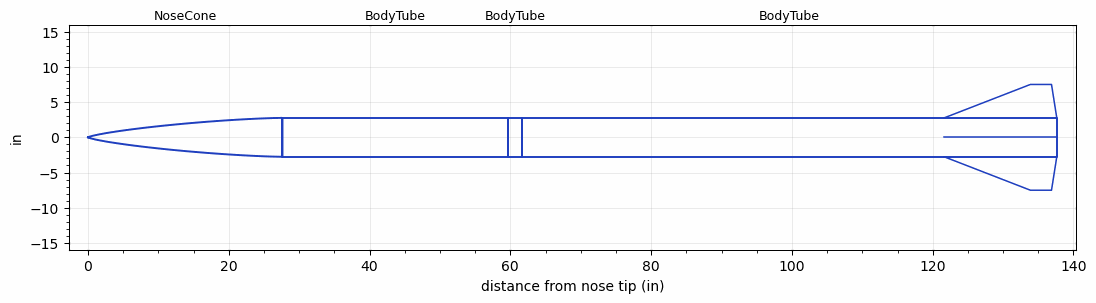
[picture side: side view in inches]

<RASAeroDocument>
 <FileVersion>2</FileVersion>
 <RocketDesign>
  <NoseCone>
   <Length>27.6249</Length>
   <Diameter>5.525</Diameter>
   <Shape>Von Karman Ogive</Shape>
   <Location>0</Location>
  </NoseCone>
  <BodyTube>
   <Length>31.9999</Length>
   <Diameter>5.525</Diameter>
   <Location>27.6249</Location>
  </BodyTube>
  <BodyTube>
   <Length>2</Length>
   <Diameter>5.525</Diameter>
   <Location>59.6249</Location>
  </BodyTube>
  <BodyTube>
   <Length>75.9998</Length>
   <Diameter>5.525</Diameter>
   <Location>61.6249</Location>
   <Fin>
    <Count>4</Count>
    <Chord>16</Chord>
    <Span>4.75</Span>
    <SweepDistance>12.2515</SweepDistance>
    <TipChord>3</TipChord>
    <Thickness>0.5</Thickness>
    <Location>16</Location>
    <AirfoilSection>Subsonic NACA</AirfoilSection>
   </Fin>
  </BodyTube>
  <Surface>Smooth Paint</Surface>
  <ModifiedBarrowman>False</ModifiedBarrowman>
  <Turbulence>False</Turbulence>
  <UseBooster1>False</UseBooster1>
  <UseBooster2>False</UseBooster2>
 </RocketDesign>
 <LaunchSite>
  <Altitude>3005</Altitude>
  <Pressure>29.92</Pressure>
  <RodAngle>0</RodAngle>
  <RodLength>17</RodLength>
  <Temperature>100</Temperature>
  <WindSpeed>5</WindSpeed>
 </LaunchSite>
 <Recovery>
  <Altitude1>656.168</Altitude1>
  <Altitude2>1500</Altitude2>
  <DeviceType1>Parachute</DeviceType1>
  <DeviceType2>Parachute</DeviceType2>
  <Event1>True</Event1>
  <Event2>True</Event2>
  <Size1>36</Size1>
  <Size2>143.9997</Size2>
  <EventType1>Apogee</EventType1>
  <EventType2>Altitude</EventType2>
  <CD1>0.97</CD1>
  <CD2>2.2</CD2>
 </Recovery>
 <SimulationList>
  <Simulation>
   <SustainerEngine>O5500X  (AT)</SustainerEngine>
   <SustainerLaunchWt>71.7</SustainerLaunchWt>
   <SustainerNozzleDiameter>3</SustainerNozzleDiameter>
   <SustainerCG>94.13</SustainerCG>
   <SustainerIgnitionDelay>0</SustainerIgnitionDelay>
   <Booster1SeparationDelay>0</Booster1SeparationDelay>
   <Booster1IgnitionDelay>0</Booster1IgnitionDelay>
   <IncludeBooster1>False</IncludeBooster1>
   <Booster2Delay>0</Booster2Delay>
   <IncludeBooster2>False</IncludeBooster2>
   <TimetoApogee>40.88914</TimetoApogee>
   <MaxAltitude>32501.06</MaxAltitude>
   <MaxVelocity>2160.328</MaxVelocity>
  </Simulation>
  <Simulation>
   <SustainerLaunchWt>71.7356</SustainerLaunchWt>
   <SustainerCG>94.1344</SustainerCG>
   <SustainerIgnitionDelay>0</SustainerIgnitionDelay>
   <Booster1SeparationDelay>0</Booster1SeparationDelay>
   <Booster1IgnitionDelay>0</Booster1IgnitionDelay>
   <IncludeBooster1>False</IncludeBooster1>
   <Booster2Delay>0</Booster2Delay>
   <IncludeBooster2>False</IncludeBooster2>
  </Simulation>
  <Simulation>
   <SustainerLaunchWt>70.6278</SustainerLaunchWt>
   <SustainerCG>96.5985</SustainerCG>
   <SustainerIgnitionDelay>0</SustainerIgnitionDelay>
   <Booster1SeparationDelay>0</Booster1SeparationDelay>
   <Booster1IgnitionDelay>0</Booster1IgnitionDelay>
   <IncludeBooster1>False</IncludeBooster1>
   <Booster2Delay>0</Booster2Delay>
   <IncludeBooster2>False</IncludeBooster2>
  </Simulation>
  <Simulation>
   <SustainerLaunchWt>64.0745</SustainerLaunchWt>
   <SustainerCG>96.9611</SustainerCG>
   <SustainerIgnitionDelay>0</SustainerIgnitionDelay>
   <Booster1SeparationDelay>0</Booster1SeparationDelay>
   <Booster1IgnitionDelay>0</Booster1IgnitionDelay>
   <IncludeBooster1>False</IncludeBooster1>
   <Booster2Delay>0</Booster2Delay>
   <IncludeBooster2>False</IncludeBooster2>
  </Simulation>
  <Simulation>
   <SustainerLaunchWt>71.7356</SustainerLaunchWt>
   <SustainerCG>94.1344</SustainerCG>
   <SustainerIgnitionDelay>0</SustainerIgnitionDelay>
   <Booster1SeparationDelay>0</Booster1SeparationDelay>
   <Booster1IgnitionDelay>0</Booster1IgnitionDelay>
   <IncludeBooster1>False</IncludeBooster1>
   <Booster2Delay>0</Booster2Delay>
   <IncludeBooster2>False</IncludeBooster2>
  </Simulation>
 </SimulationList>
</RASAeroDocument>
